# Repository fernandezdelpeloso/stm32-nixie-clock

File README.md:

# STM32 Nixie Clock (R|Z568M)

**TL;DR:** One-tube Nixie clock (Dalibor Farny R|Z568M) on an STM32 Cortex-M4F with GPS time sync, RTC backup, and anti–cathode-poisoning routine.

[▶ Short demo (MP4)](media/videos/bright.mp4)

## Hardware
- MCU: STM32L4A6RGT7
- Level shifting: PCA9306 (custom module)
- HV driver: K155ID1 (5 V logic)
- Time: NEO-M8N (UTC) + DS3231 (backup)

### Files in this repo
- Schematics (PDF): `hardware/exports/schematic/`
- PCB (design): `hardware/exporta/pcb`
- 3D (PCB model): `hardware/exports/3d/`
- BOM (CSV + iBOM): `hardware/exports/bom/`
- Native KiCad project: `hardware/kicad/`

## Firmware
`firmware/` (STM32CubeIDE project). Roadmap: GPS/NMEA parse, RTC sync, presence sensor → anti-poisoning routine, optional FreeRTOS + SystemView.

## Safety
**High voltage present.** Observe clearance/creepage and safe handling.

## License
MIT

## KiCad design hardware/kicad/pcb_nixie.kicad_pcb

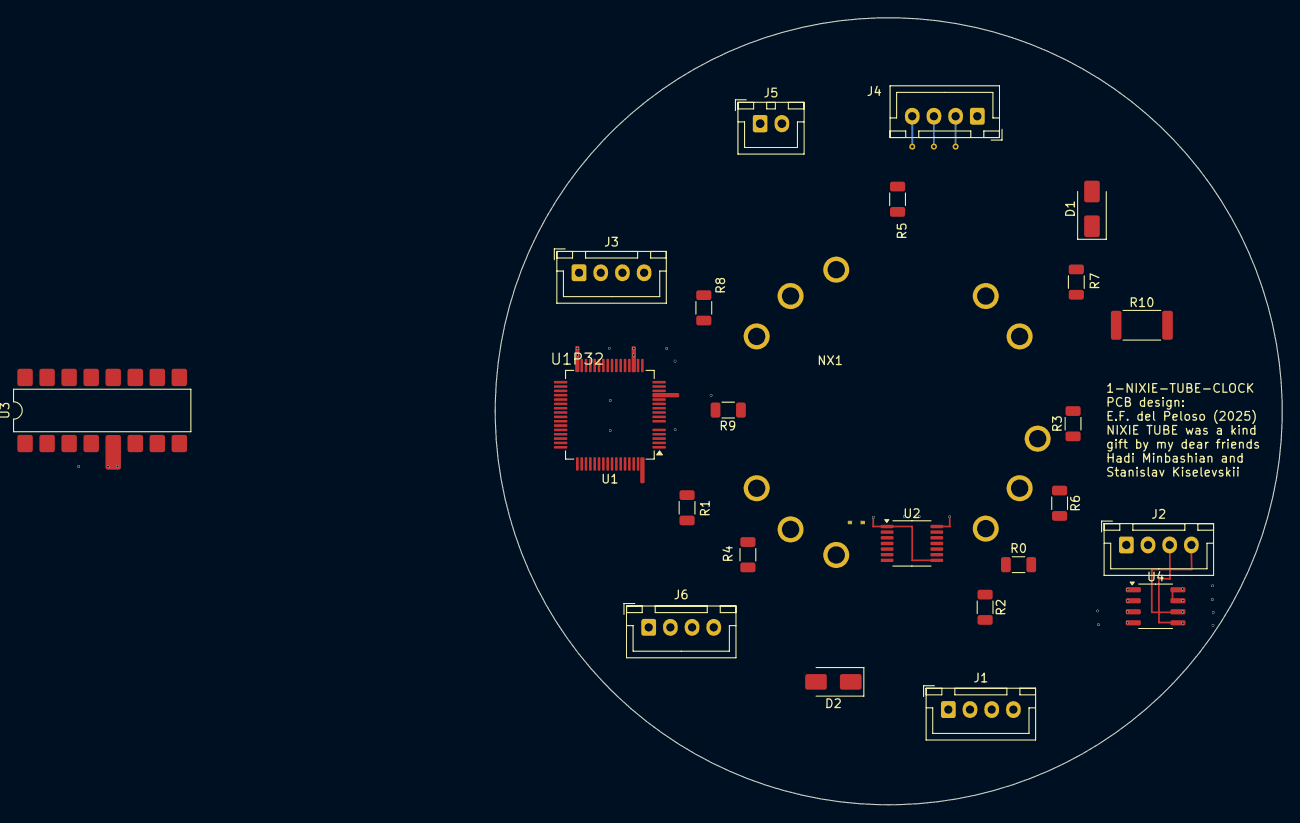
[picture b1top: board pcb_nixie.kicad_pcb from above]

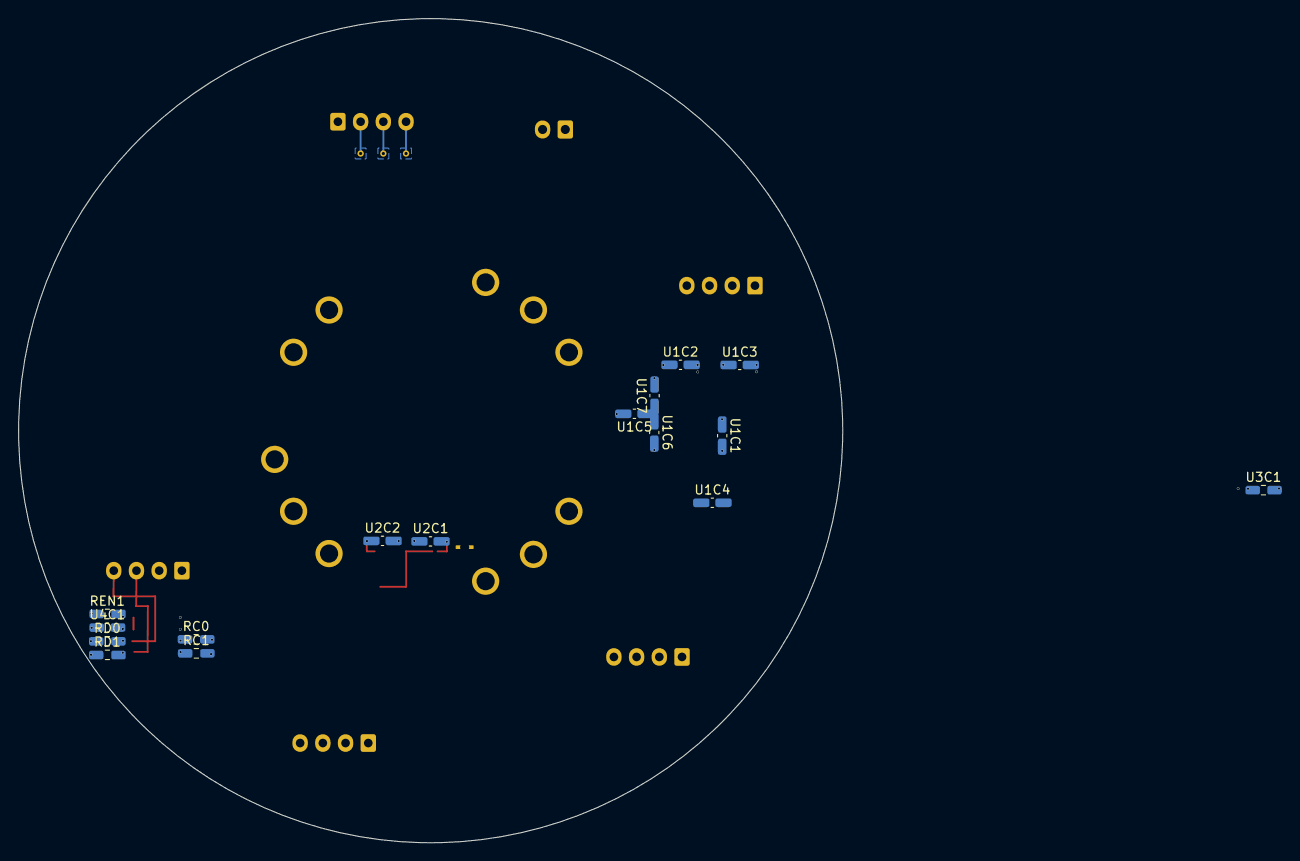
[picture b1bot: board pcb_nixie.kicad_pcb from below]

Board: 6 copper layers, 90.7 x 90.7 mm, 44 parts (16 on the bottom side), 45 nets, no tracks yet.

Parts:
D1: US1M_R3G; D_SMA
D2: SMAJ170A; D_SMA
J1: MCU-SWD; JST_XH_B4B-XH-A_1x04_P2.50mm_Vertical
J2: Omron; JST_XH_B4B-XH-A_1x04_P2.50mm_Vertical
J3: GPS-M8N; JST_XH_B4B-XH-A_1x04_P2.50mm_Vertical
J4: Power-supply; JST_XH_B4B-XH-A_1x04_P2.50mm_Vertical
J4P2, J4P3, J4P4: (no value)
J5: Littelfuse-0218.020HXP; JST_XH_B2B-XH-A_1x02_P2.50mm_Vertical
J6: OLED; JST_XH_B4B-XH-A_1x04_P2.50mm_Vertical
NX1: FRONT; nixie_socket_manual
R0: 1k2; R_1206_3216Metric
R1: 4k7; R_1206_3216Metric
R2, R5, R6: 1k1; R_1206_3216Metric
R3: 1k5; R_1206_3216Metric
R4: 3k3; R_1206_3216Metric
R7: 3k6; R_1206_3216Metric
R8: 0R; R_1206_3216Metric
R9: 1k; R_1206_3216Metric
R10: 4k7; R_2512_6332Metric
RC0, RC1: 10k; R_0603_1608Metric
RD0, RD1: 10k; R_0603_1608Metric
REN1: 200k; R_0603_1608Metric
U1: STM32L4A6RGTx; LQFP-64_10x10mm_P0.5mm
U1C1: 4.7U; C_0603_1608Metric
U1C2, U1C3, U1C4, U1C5, U1C6, U1C7, U2C1, U2C2: 100N; C_0603_1608Metric
U1P32: (no value)
U2: TXB0104PW; TSSOP-14_4.4x5mm_P0.65mm
U3: K155id1; SMDIP-16_W7.62mm
U3C1: 1U; R_0603_1608Metric
U4: PCA9306D; SO-8_3.9x4.9mm_P1.27mm
U4C1: 100P; C_0603_1608Metric

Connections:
+3V3: J3.4 (+3V3), J4.4 (3V3), J4P4.17, J6.3 (3V3), RC0.2, RC1.1, U1.1 (VBAT), U1.13 (VDDA), U1.19 (VDD), U1.32 (VDD), U1.48 (VDDUSB), U1C1.2, U1C2.2, U1P32.32 (VDD), U2.1 (VCCA), U2.8 (OE), U4.2 (VREF1)
+5V: J2.2 (+5V), J4.3 (5V), J4P3.16, RD0.2, RD1.1, REN1.1, REN1.2, U2.14 (VCCB), U4.7 (VREF2), U4.8 (EN)
/A1: U1.14 (PA0), U2.2 (A1)
/A2: U1.15 (PA1), U2.3 (A2)
/A3: U1.20 (PA4), U2.4 (A3)
/A4: U1.21 (PA5), U2.5 (A4)
/B1: U2.13 (B1), U3.3 (A)
/B2: U2.12 (B2), U3.6 (B)
/B3: U2.11 (B3), U3.7 (C)
/B4: U2.10 (B4), U3.4 (D)
/PCA9306/SCL: RC0.1, U1.61 (PB8), U4.3 (SCL1)
/PCA9306/SDA: U1.62 (PB9), U4.4 (SDA1)
/RA0: R0.1, U3.16 (0)
/RA1: R1.2, U3.15 (1)
/RA2: R2.1, U3.8 (2)
/RA3: R3.1, U3.9 (3)
/RA4: R4.1, U3.13 (4)
/RA5: R5.1, U3.14 (5)
/RA6: R6.2, U3.11 (6)
/RA7: R7.1, U3.10 (7)
/RA8: R8.2, U3.1 (8)
/RA9: R9.1, U3.2 (9)
/RB0: NX1.0, R0.2
/RB1: NX1.1, R1.1
/RB2: NX1.2, R2.2
/RB3: NX1.3, R3.2
/RB4: NX1.4, R4.2
/RB5: NX1.5, R5.2
/RB6: NX1.6, R6.1
/RB7: NX1.7, R7.2
/RB8: NX1.8, R8.1
/RB9: NX1.9, R9.2
GND: D1.2 (A), D2.2 (A2), J1.3 (GND), J2.1 (GND), J3.1 (GND), J4.2 (GND), J4P2.15, J6.4 (GND), U1.12 (VSSA), U1.18 (VSS), U1.31 (VSS), U1.47 (VSS), U1.63 (VSS), U1C1.1, U1C3.2, U1C4.1, U2.7 (GND), U3.12 (GND), U4C1.1, U4C1.2
HT: D2.1 (A1), J4.1 (170V), J5.1
unnamed: D1.1 (K), NX1.10, R10.2
unnamed: J1.4 (RST), U1.7 (NRST)
unnamed: J1.1 (SWCLK), U1.49 (PA14)
unnamed: J1.2 (SWDIO), U1.46 (PA13)
unnamed: J2.4 (SCL), RD0.1, U4.6 (SCL2)
unnamed: J2.3 (SDA), RD1.2, U4.5 (SDA2)
unnamed: J3.2 (Rx), U1.30 (PB11)
unnamed: J3.3 (Tx), U1.24 (PC4)
unnamed: J5.2, R10.1
unnamed: J6.1 (SCL), U1.58 (PB6)
unnamed: J6.2 (SDA), U1.59 (PB7)

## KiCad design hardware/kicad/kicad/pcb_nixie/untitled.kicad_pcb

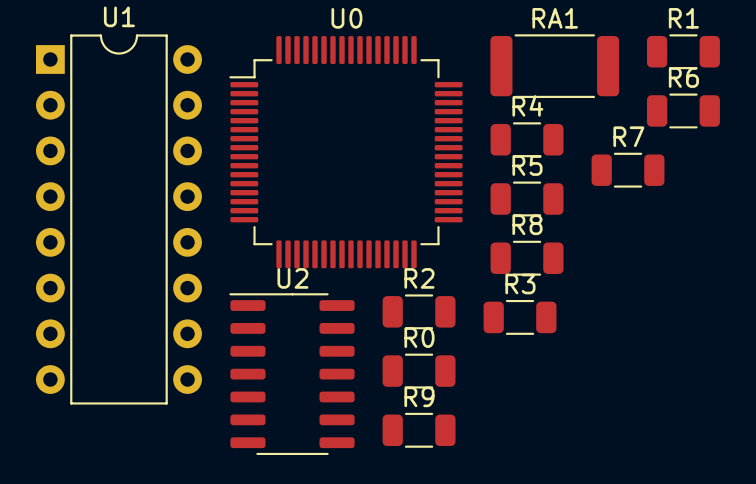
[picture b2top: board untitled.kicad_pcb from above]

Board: 2 copper layers, 14 parts (0 on the bottom side), 19 nets, no tracks yet.

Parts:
R0: 1k2; R_1206_3216Metric
R1: 4k7; R_1206_3216Metric
R2, R5, R6: 1k1; R_1206_3216Metric
R3: 1k5; R_1206_3216Metric
R4: 3k3; R_1206_3216Metric
R7: 3k6; R_1206_3216Metric
R8: 0R; R_1206_3216Metric
R9: 1k; R_1206_3216Metric
RA1: 4k7; R_2512_6332Metric
U0: STM32F103RCT6; LQFP-64_10x10mm_P0.5mm
U1: 155ИД1; DIP-16_W7.62mm
U2: TXB0104D; SOIC-14_3.9x8.7mm_P1.27mm

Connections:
+5V: U1.5 (VCC), U2.14 (VCCB)
unnamed: R0.1, U1.16 (0)
unnamed: R1.2, U1.15 (1)
unnamed: R2.1, U1.8 (2)
unnamed: R3.1, U1.9 (3)
unnamed: R4.1, U1.13 (4)
unnamed: R5.1, U1.14 (5)
unnamed: R6.2, U1.11 (6)
unnamed: R7.1, U1.10 (7)
unnamed: R8.2, U1.1 (8)
unnamed: R9.1, U1.2 (9)
unnamed: U0.14 (PA0), U2.2 (A1)
unnamed: U0.15 (PA1), U2.3 (A2)
unnamed: U0.16 (PA2), U2.4 (A3)
unnamed: U0.17 (PA3), U2.5 (A4)
unnamed: U1.3 (A), U2.13 (B1)
unnamed: U1.4 (D), U2.10 (B4)
unnamed: U1.6 (B), U2.12 (B2)
unnamed: U1.7 (C), U2.11 (B3)

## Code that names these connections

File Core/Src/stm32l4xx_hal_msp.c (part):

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
    __HAL_RCC_GPIOB_CLK_ENABLE();
    /**I2C1 GPIO Configuration
    PB8     ------> I2C1_SCL
    PB9     ------> I2C1_SDA
    */
    GPIO_InitStruct.Pin = GPIO_PIN_8|GPIO_PIN_9;
    GPIO_InitStruct.Mode = GPIO_MODE_AF_OD;
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
    __HAL_RCC_GPIOB_CLK_ENABLE();
    /**I2C4 GPIO Configuration
    PB6     ------> I2C4_SCL
    PB7     ------> I2C4_SDA
    */
    GPIO_InitStruct.Pin = GPIO_PIN_6|GPIO_PIN_7;
    GPIO_InitStruct.Mode = GPIO_MODE_AF_OD;
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    __HAL_RCC_I2C1_CLK_DISABLE();

    /**I2C1 GPIO Configuration
    PB8     ------> I2C1_SCL
    PB9     ------> I2C1_SDA
    */
    HAL_GPIO_DeInit(GPIOB, GPIO_PIN_8);

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    __HAL_RCC_I2C4_CLK_DISABLE();

    /**I2C4 GPIO Configuration
    PB6     ------> I2C4_SCL
    PB7     ------> I2C4_SDA
    */
    HAL_GPIO_DeInit(GPIOB, GPIO_PIN_6);

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
    __HAL_RCC_GPIOA_CLK_ENABLE();
    /**USART2 GPIO Configuration
    PA2     ------> USART2_TX
    PA3     ------> USART2_RX
    */
    GPIO_InitStruct.Pin = GPIO_PIN_2|GPIO_PIN_3;
    GPIO_InitStruct.Mode = GPIO_MODE_AF_PP;
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    __HAL_RCC_GPIOC_CLK_ENABLE();
    __HAL_RCC_GPIOB_CLK_ENABLE();
    /**USART3 GPIO Configuration
    PC4     ------> USART3_TX
    PB11     ------> USART3_RX
    */
    GPIO_InitStruct.Pin = GPIO_PIN_4;
    GPIO_InitStruct.Mode = GPIO_MODE_AF_PP;
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    __HAL_RCC_USART2_CLK_DISABLE();

    /**USART2 GPIO Configuration
    PA2     ------> USART2_TX
    PA3     ------> USART2_RX
    */
    HAL_GPIO_DeInit(GPIOA, GPIO_PIN_2|GPIO_PIN_3);

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    __HAL_RCC_USART3_CLK_DISABLE();

    /**USART3 GPIO Configuration
    PC4     ------> USART3_TX
    PB11     ------> USART3_RX
    */
    HAL_GPIO_DeInit(GPIOC, GPIO_PIN_4);

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
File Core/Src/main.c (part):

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  /*Configure GPIO pin Output Level */
  HAL_GPIO_WritePin(GPIOA, GPIO_PIN_0|GPIO_PIN_1|GPIO_PIN_4|GPIO_PIN_5, GPIO_PIN_RESET);

  /*Configure GPIO pins : PA0 PA1 PA4 PA5 */
  GPIO_InitStruct.Pin = GPIO_PIN_0|GPIO_PIN_1|GPIO_PIN_4|GPIO_PIN_5;
  GPIO_InitStruct.Mode = GPIO_MODE_OUTPUT_PP;
  GPIO_InitStruct.Pull = GPIO_NOPULL;
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
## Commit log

2025-08-13 Initial commit: STM32 code, KiCad project, and documentation
2025-08-13 Correcting problems with duplicate folders
2025-08-29 keep on working the schematics and PCB

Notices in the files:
Core/Src/main.c:
Copyright (c) 2025 STMicroelectronics.
All rights reserved.
This software is licensed under terms that can be found in the LICENSE file
